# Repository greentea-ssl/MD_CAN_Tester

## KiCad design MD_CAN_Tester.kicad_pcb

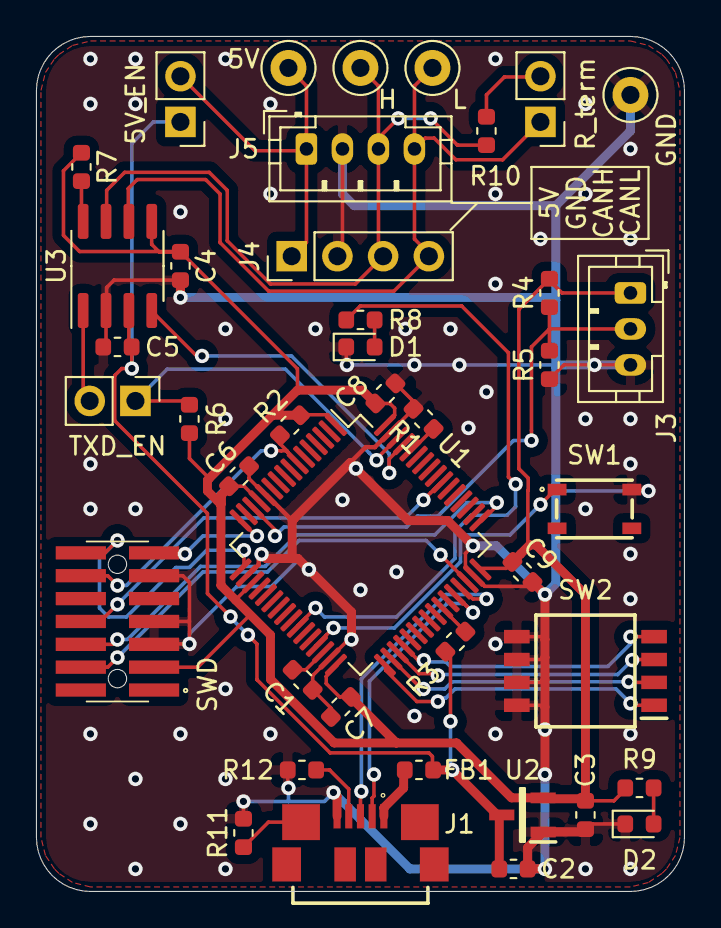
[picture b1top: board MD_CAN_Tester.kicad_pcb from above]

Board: 2 copper layers, 36.0 x 47.5 mm, 41 parts (0 on the bottom side), 34 nets.

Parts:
5V: TP_5V; TestPoint_Loop_D2.50mm_Drill1.0mm_LowProfile
5V_EN: CAN5V_EN; PinHeader_1x02_P2.54mm_Vertical
C1: 4.7u; C_0603_1608Metric
C2, C3, C4, C5, C6, C7, C8, C9: 0.1u; C_0603_1608Metric
D1: USER_LED; LED_0603_1608Metric
D2: 3V3_LED; LED_0603_1608Metric
FB1: Ferrite_Bead; L_0603_1608Metric
GND: TP_GND; TestPoint_Loop_D2.50mm_Drill1.0mm_LowProfile
H: TP_CANH; TestPoint_Loop_D2.50mm_Drill1.0mm_LowProfile
J1: USB_B_Micro; ZX62R-B-5P
J3: AnalogInput; JST_PH_B3B-PH-K_1x03_P2.00mm_Vertical
J4: PinHeader; PinHeader_1x04_P2.54mm_Vertical
J5: CAN_Connector; JST_PH_B4B-PH-K_1x04_P2.00mm_Vertical
L: TP_CANL; TestPoint_Loop_D2.50mm_Drill1.0mm_LowProfile
R1, R2, R3, R6, R7: 10k; R_0603_1608Metric
R4, R5: 1M; R_0603_1608Metric
R8, R9: 1k; R_0603_1608Metric
R10: 120R; R_0603_1608Metric
R11, R12: 0R; R_0603_1608Metric
R_term: Rteam_EN; PinHeader_1x02_P2.54mm_Vertical
SW1: USER_BUTTON; SKRPACE010
SW2: ID_SELECT; SOIC127P812X230-8N
SWD: SWD; FTSH-107-XX-YYY-DV-K-A-TR
TXD_EN: TXD_EN; PinHeader_1x02_P2.54mm_Vertical
U1: STM32F446RETx; LQFP-64_10x10mm_P0.5mm
U2: MCP1703A-3302_SOT23; SOT95P255X145-3N
U3: MCP2562-E-SN; SOIC-8_3.9x4.9mm_P1.27mm

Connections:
+3V3: C3.1, C4.1, C6.1, C7.1, C8.1, C9.1, J3.1, R2.1, R4.2, R6.1, R7.1, R9.2, SWD.3, U1.1, U1.13, U1.19, U1.32, U1.48, U1.64, U2.2, U3.5
+5V: 5V_EN.1, C2.1, C5.1, FB1.1, R3.1, U2.3, U3.3
/CAN1_RX: U1.61, U3.4
/CAN1_TX: R6.2, TXD_EN.1, U1.62
/DIPSW_1: SW2.1, U1.33
/DIPSW_2: SW2.2, U1.34
/DIPSW_3: SW2.3, U1.35
/DIPSW_4: SW2.4, U1.36
/USB_DM: J1.2, U1.44
/USB_DP: J1.3, U1.45
GND: C1.2, C2.2, C3.2, C4.2, C5.2, C6.2, C7.2, C8.2, C9.2, D1.1, D2.1, GND.1, J1.5, J3.3, J4.2, J5.2, R1.2, R5.1, R11.2, R12.2, SW1.2, SW2.5, SW2.6, SW2.7, SW2.8, SWD.5, SWD.7, SWD.11, U1.12, U1.18, U1.31, U1.47, U1.63, U2.1, U3.2
unnamed: C1.1, U1.30
unnamed: D1.2, R8.1
unnamed: D2.2, R9.1
unnamed: FB1.2, J1.1
unnamed: J1.4, R12.1
unnamed: J1.6, R11.1
unnamed: J3.2, R4.1, R5.2, U1.14
unnamed: 5V.1, 5V_EN.2, J4.1, J5.1
unnamed: H.1, J4.3, J5.3, R10.2, U3.7
unnamed: J4.4, J5.4, L.1, R_term.1, U3.6
unnamed: TXD_EN.2, U3.1
unnamed: R10.1, R_term.2
unnamed: R1.1, U1.60
unnamed: R3.2, U1.42
unnamed: R7.2, U3.8
unnamed: R8.2, U1.26
unnamed: SW1.1, U1.29
T_NRST: R2.2, SWD.12, U1.7
T_SWCLK: SWD.6, U1.49
T_SWDIO: SWD.4, U1.46
T_SWO: SWD.8, U1.55
T_VCP_RX: SWD.13, U1.16
T_VCP_TX: SWD.14, U1.17

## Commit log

2020-08-31 add: プロジェクト追加
2020-09-01 add: 回路図追加
2020-09-01 CAN5Vにジャンパ追加
2020-09-01 Add: フットプリントの割り付け完了
2020-09-02 GND以外ほぼ配線済み
2020-09-03 配線完了
2020-09-03 製造用に基板配置、ガーバー生成
